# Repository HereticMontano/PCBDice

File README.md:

# Electric dice

This is my first electronic project, it was inspired by this video (https://www.youtube.com/watch?v=EbNv-qJeaCI). 
I follow most of his premise, but use it to create the schema, the PCB and a functional prototype. 

## Objective
Create a virtual 6 faces dice.
When push the button, it fire the clock to send an astable signal to the IC counter from 1 to 7 (the 7 it will restar the counter).

It can handle the 6 posible state, only managmente 4 groups of leds.

```
*2     *5 
*3  *1 *6
*4     *7
```

- The led 1 it will be ON to reresent the numbers 1, 3 and 5.
- The led 4 and 5 it will be always ON excepto when need to represent the number 1.
- The led 2 and 7 it will be ON to reresent the numbers 4, 5 and 6.
- The led 3 and 6 it will be ON to reresent the numbers 6.

## First step (Schema)
Learn how to use KICad and how to make a schema, and some of good practice/convention to do it.
I had to re do a cuple of time to improve the readability of it, in the first version the lines are all over the place.

## Second step (Prototype)  

Learn to solder and use bigger PCB board next time. 
Using this small PCB to following the conection from on leg to another was a nighmare, and have no room to add the resitance in his respective holes.  

## Therd step (PCB)

Keep learning KiCad and how to use the PCB Editor, managment the footprint of the diferente components

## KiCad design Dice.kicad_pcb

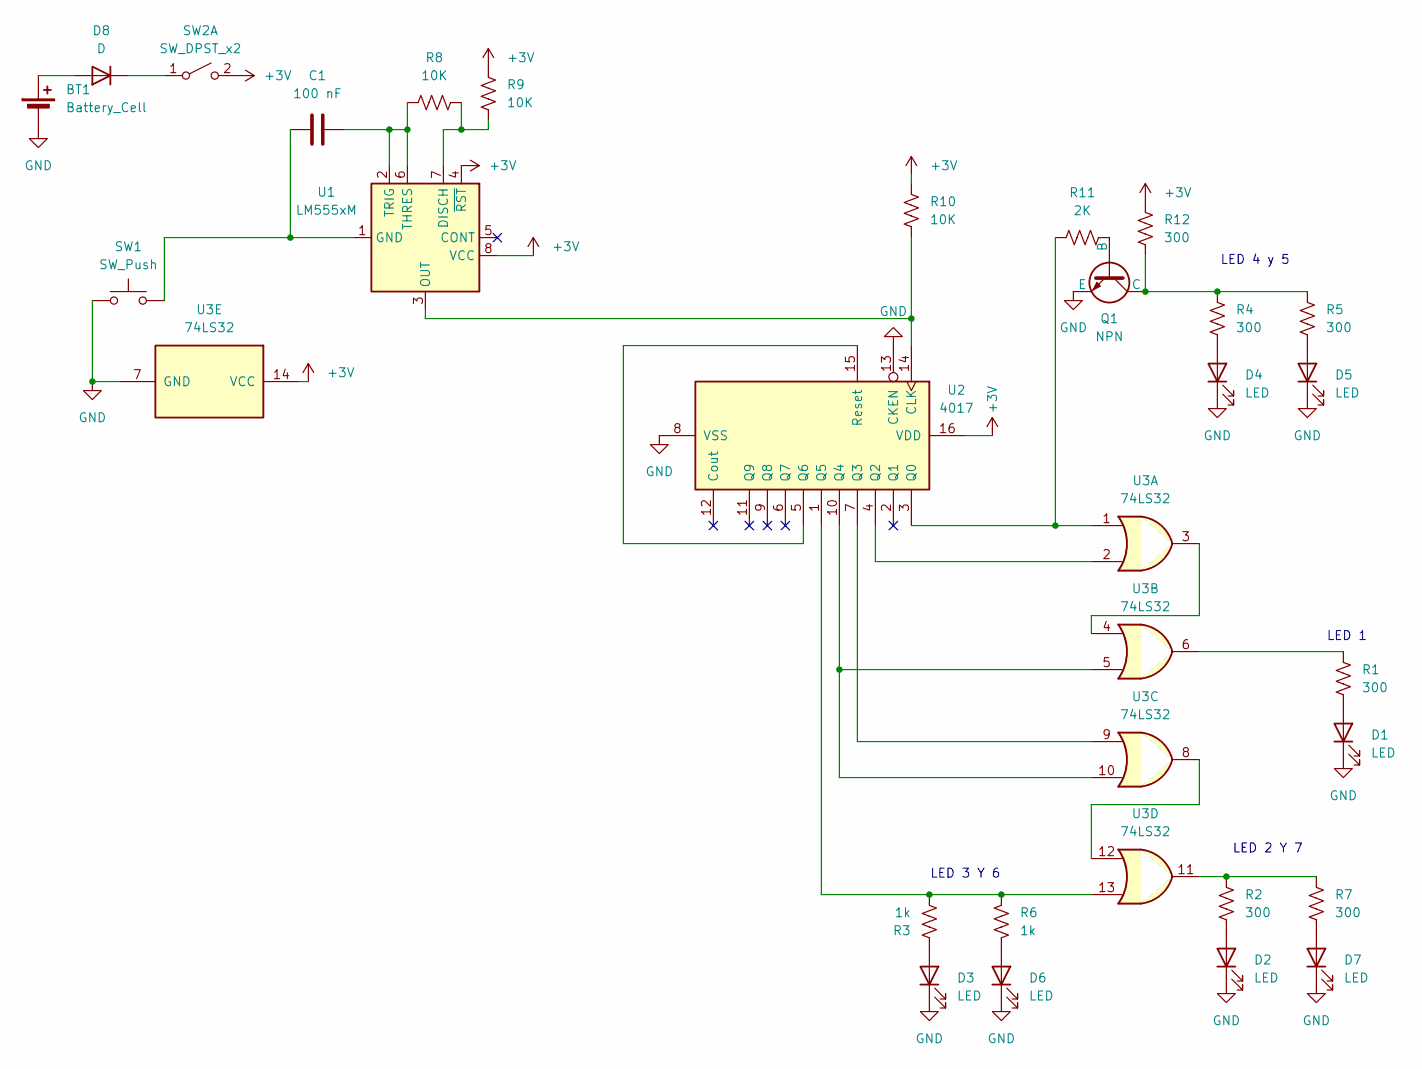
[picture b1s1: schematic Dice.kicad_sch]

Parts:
BT1: Battery_Cell; BatteryHolder_Keystone_103_1x20mm
C1: 100 nF; C_Disc_D5.0mm_W2.5mm_P2.50mm
D1, D2, D3, D4, D5, D6, D7: LED; LED_D5.0mm
D8: D; D_DO-41_SOD81_P10.16mm_Horizontal
Q1: NPN; TO-92_Inline
R1, R2, R4, R5, R7, R12: 300; R_Axial_DIN0204_L3.6mm_D1.6mm_P5.08mm_Horizontal
R3, R6: 1k; R_Axial_DIN0204_L3.6mm_D1.6mm_P5.08mm_Horizontal
R8, R9, R10: 10K; R_Axial_DIN0204_L3.6mm_D1.6mm_P5.08mm_Horizontal
R11: 2K; R_Axial_DIN0204_L3.6mm_D1.6mm_P5.08mm_Horizontal
SW1: SW_Push; SW_PUSH-12mm_Wuerth-430476085716
SW2: SW_DPST_x2; SW_Slide-03_Wuerth-WS-SLTV_10x2.5x6.4_P2.54mm
U1: LM555xM; DIP-8_W7.62mm
U2: 4017; DIP-16_W7.62mm
U3: 74LS32; DIP-14_W7.62mm

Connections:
+3V: R9.2, R10.1, R12.2, SW2.2 (B), U1.4 (~RST), U1.8 (VCC), U2.16 (VDD), U3.14 (VCC)
GND: BT1.2 (-), D1.1 (K), D2.1 (K), D3.1 (K), D4.1 (K), D5.1 (K), D6.1 (K), D7.1 (K), Q1.3 (E), SW1.1, U2.8 (VSS), U2.13 (CKEN), U3.7 (GND)
unnamed: BT1.1 (+), D8.2 (A)
unnamed: D1.2 (A), R1.2
unnamed: D2.2 (A), R2.2
unnamed: D3.2 (A), R3.2
unnamed: D4.2 (A), R4.2
unnamed: D5.2 (A), R5.2
unnamed: D6.2 (A), R6.2
unnamed: D7.2 (A), R7.2
unnamed: D8.1 (K), SW2.1 (A)
unnamed: Q1.2 (B), R11.2
unnamed: Q1.1 (C), R4.1, R5.1, R12.1
unnamed: R1.1, U3.6
unnamed: R2.1, R7.1, U3.11
unnamed: R8.2, R9.1, U1.7 (DISCH)
unnamed: C1.1, SW1.2, U1.1 (GND)
unnamed: R10.2, U1.3 (OUT), U2.14 (CLK)
unnamed: C1.2, R8.1, U1.2 (TRIG), U1.6 (THRES)
unnamed: R11.1, U2.3 (Q0), U3.1
unnamed: U2.4 (Q2), U3.2
unnamed: U2.7 (Q3), U3.9
unnamed: U2.10 (Q4), U3.5, U3.10
unnamed: R3.1, R6.1, U2.1 (Q5), U3.13
unnamed: U2.5 (Q6), U2.15 (Reset)
unnamed: U3.3, U3.4
unnamed: U3.8, U3.12

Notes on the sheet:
LED 4 y 5
LED 2 Y 7
LED 3 Y 6
LED 1

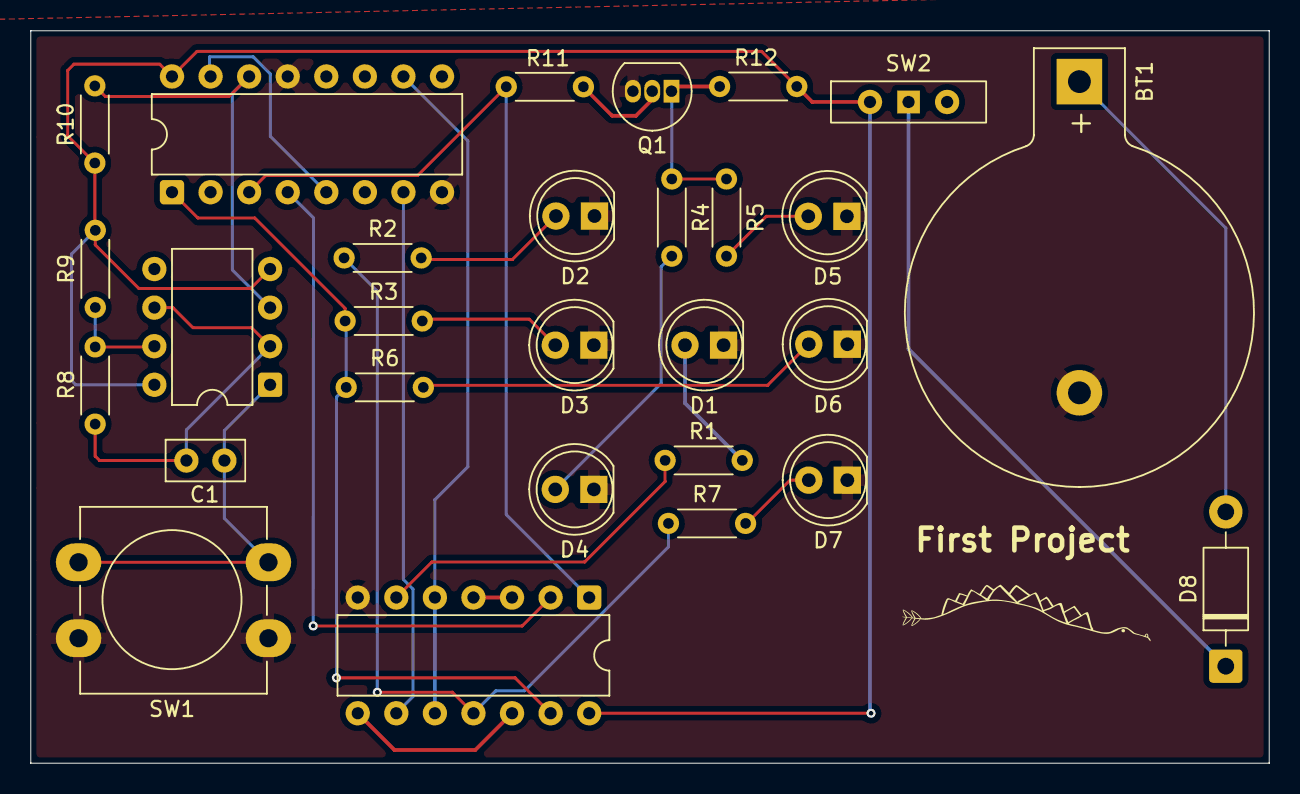
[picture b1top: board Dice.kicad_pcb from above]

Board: 2 copper layers, 81.6 x 48.2 mm, 28 parts (0 on the bottom side), 27 nets.
